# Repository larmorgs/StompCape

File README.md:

Stomp Cape
=======

Greg Larmore and Matt Moravec

This is the repository for the Stomp Cape--a BeagleBone cape for an open source guitar effects stomp pedal. The pedal will leverage the power of 32-bit embedded linux on the BeagleBone and will be reconfigurable using node.js.

Current Status
=======

Currently the schematic for the cape has been created and is being validated. Software to support the cape is under development.

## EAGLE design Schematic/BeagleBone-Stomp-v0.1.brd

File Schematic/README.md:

Stomp Cape
=======

Greg Larmore and Matt Moravec

This is the schematic for the Stomp Cape created in Eagle 6.3.0. It uses the built in Eagle libraries along with the libraries located in the ./lbr folder.

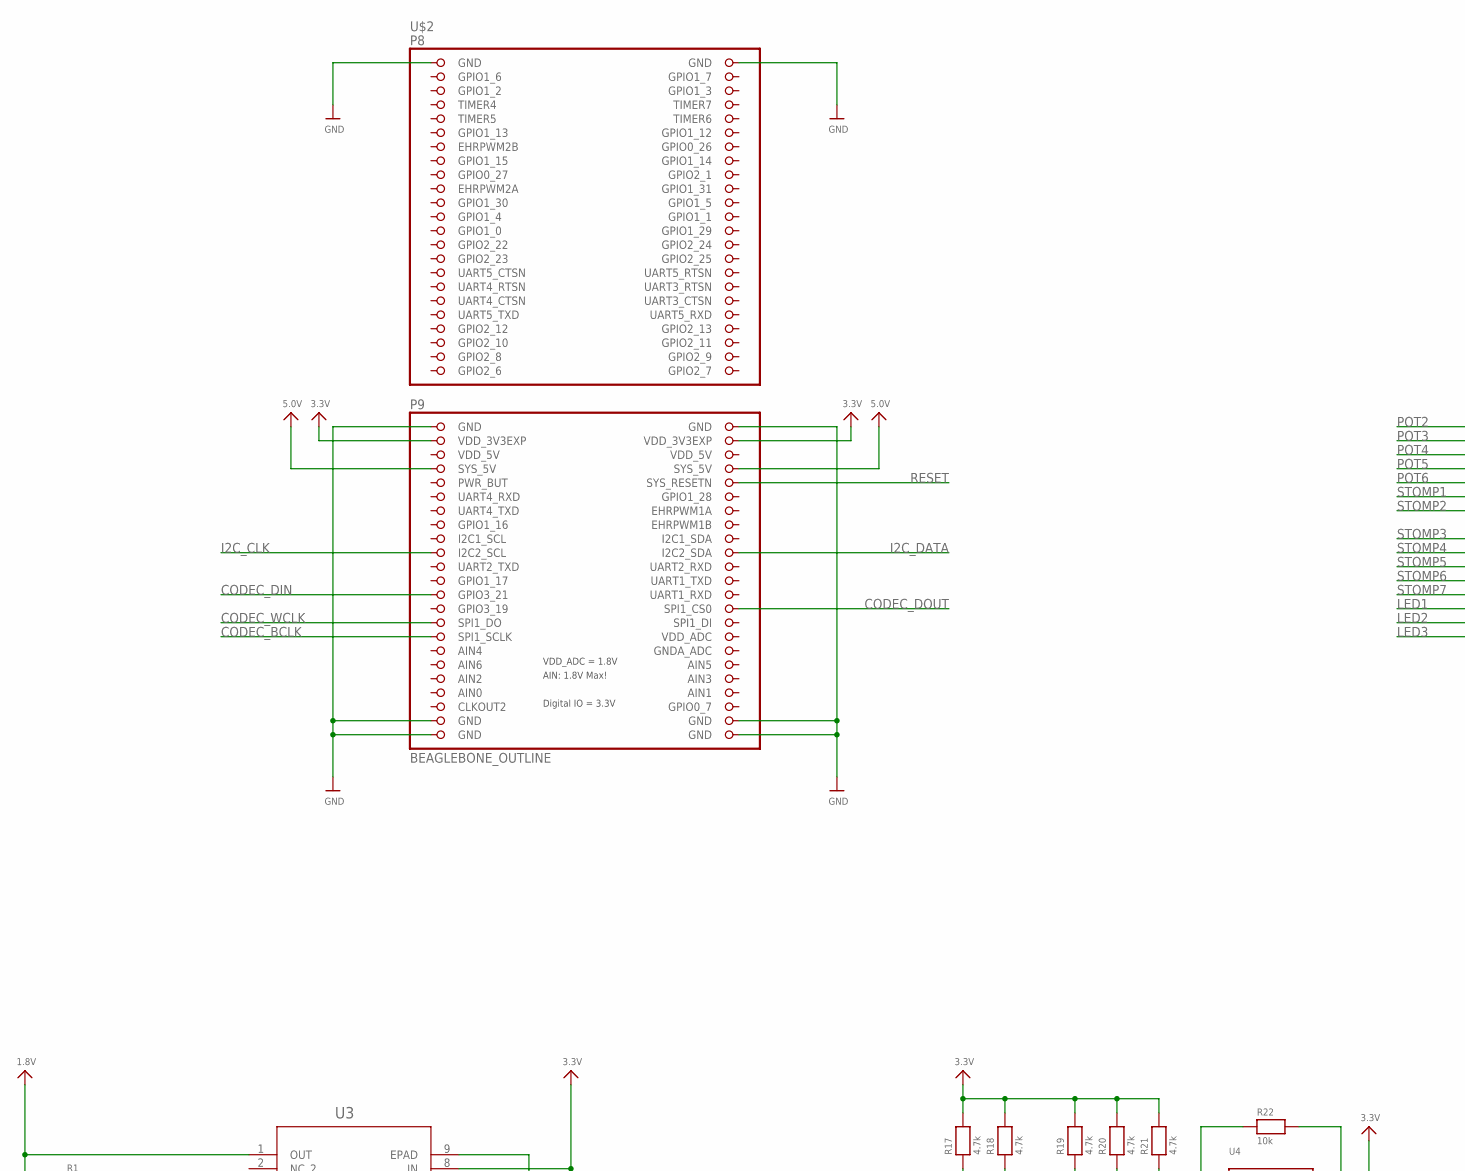
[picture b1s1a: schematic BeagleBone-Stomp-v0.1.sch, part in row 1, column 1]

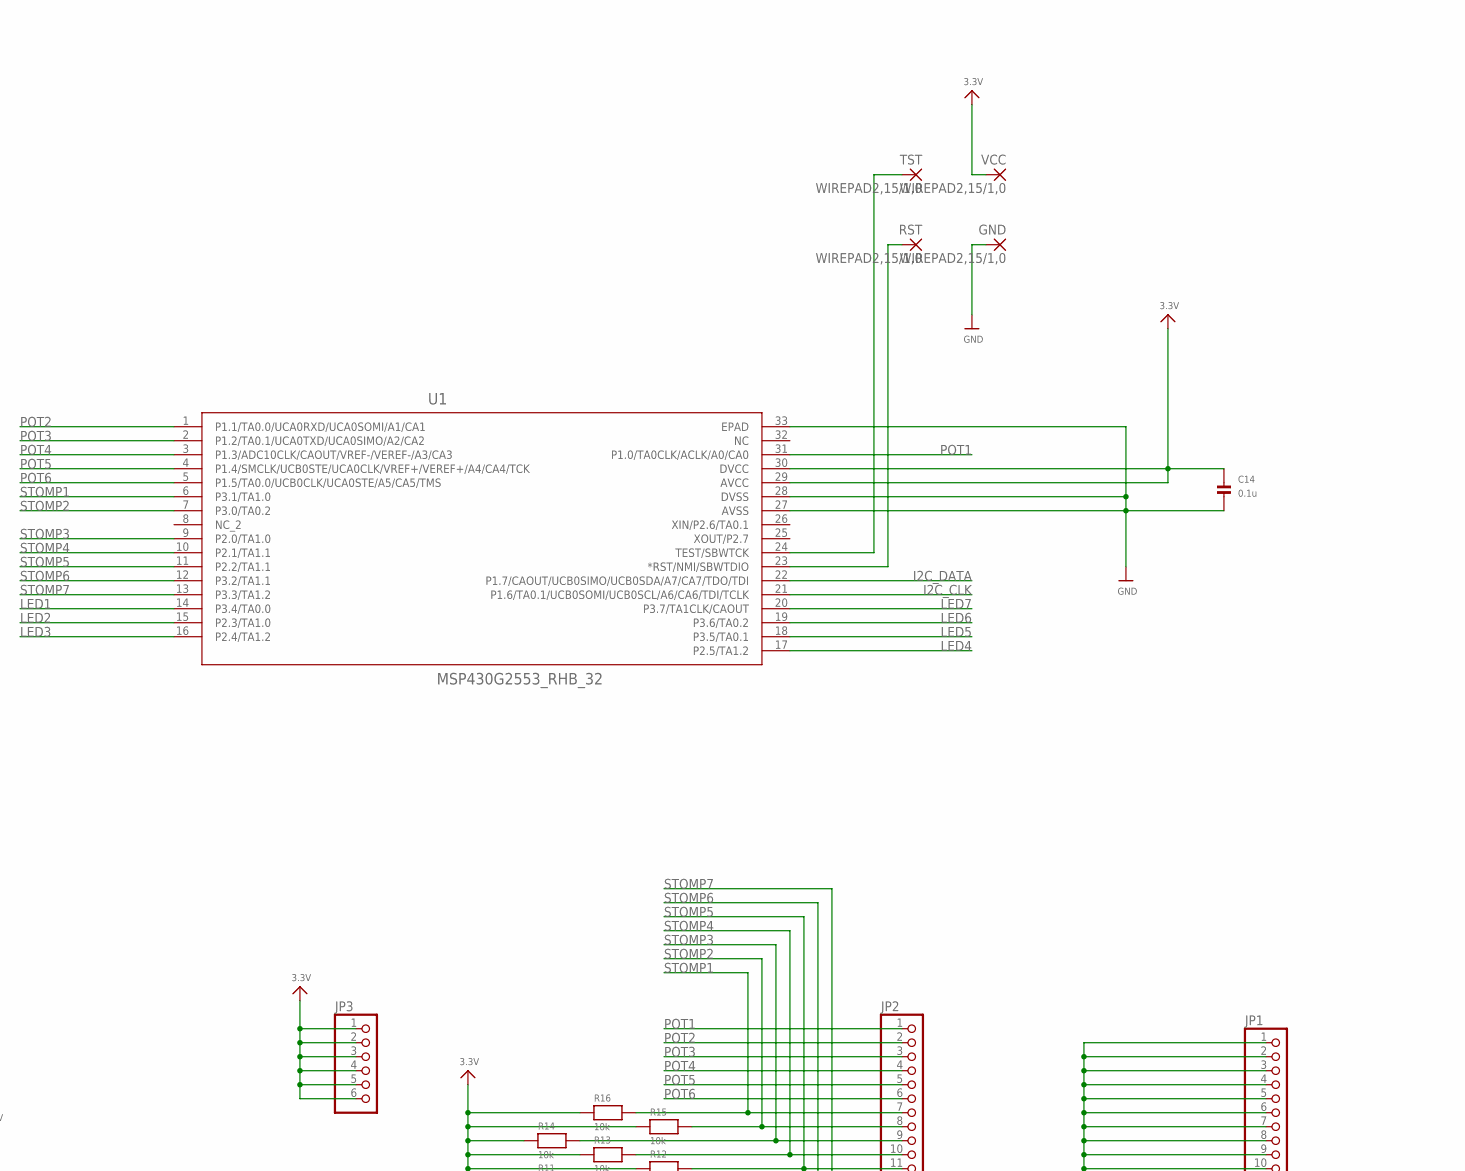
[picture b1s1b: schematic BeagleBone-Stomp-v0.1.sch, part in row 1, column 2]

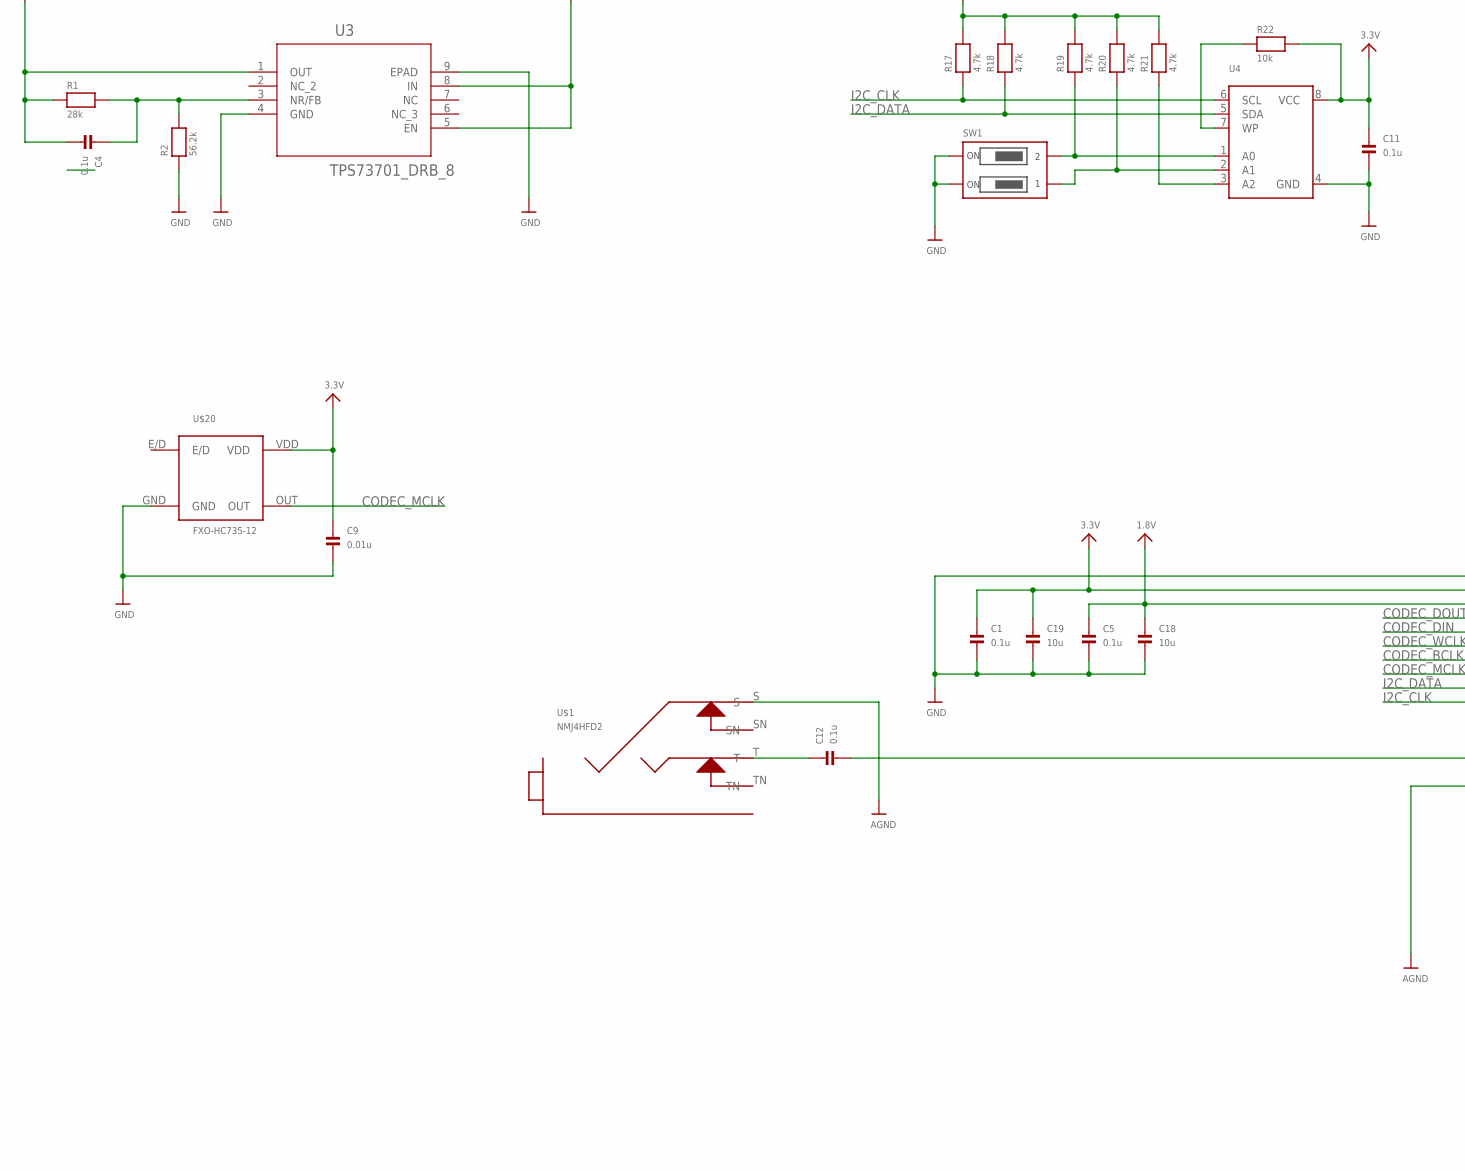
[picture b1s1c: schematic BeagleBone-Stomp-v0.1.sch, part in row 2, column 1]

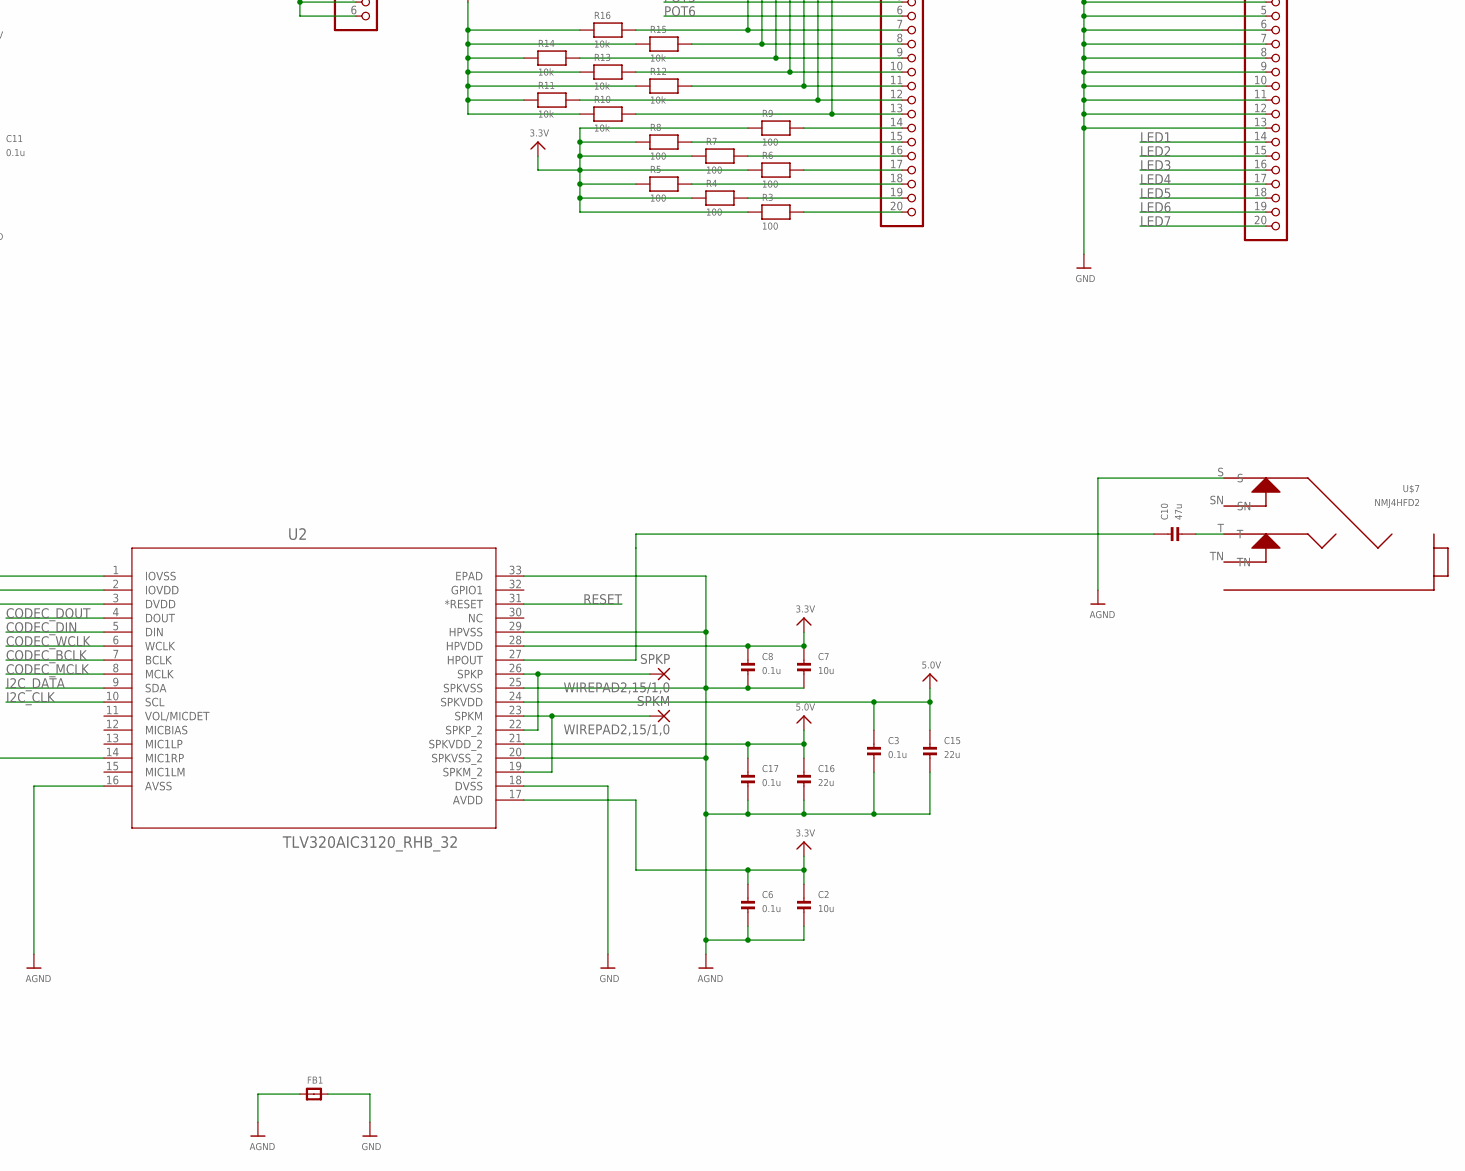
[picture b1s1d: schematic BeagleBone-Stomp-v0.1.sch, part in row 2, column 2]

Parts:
C1, C3, C4, C5, C6, C8, C11, C12, C14, C17: 0.1u; 0402
C2, C7, C18, C19: 10u; 0805
C9: 0.01u; 0402
C10: 47u; 0805
C15, C16: 22u; 0805
FB1: FERRITE_0402; _0402
GND: WIREPAD2,15/1,0; 2,15/1,0
JP1, JP2: HEADER-1X20ROUND; 1X20_ROUND
JP3: HEADER-1X6ROUND; 1X06_ROUND
R1: 28k; 0402
R2: 56.2k; 0402
R3, R4, R5, R6, R7, R8, R9: 100; 0402
R10, R11, R12, R13, R14, R15, R16, R22: 10k; 0402
R17, R18, R19, R20, R21: 4.7k; 0402
RST: WIREPAD2,15/1,0; 2,15/1,0
SPKM: WIREPAD2,15/1,0; 2,15/1,0
SPKP: WIREPAD2,15/1,0; 2,15/1,0
SW1: DIPSWITCH_2PIN
TST: WIREPAD2,15/1,0; 2,15/1,0
U1: MSP430G2553_RHB_32; RHB32_3P45X3P45
U2: TLV320AIC3120_RHB_32; RHB32_3P45X3P45
U3: TPS73701_DRB_8; DRB8_1P75X1P5
U4: EEPROM_I2C_SOIC8_GENERIC; SOIC8_150MIL
U$1, U$7: NMJ4HFD2
U$2: BEAGLEBONE_OUTLINE; BEAGLEBONE_SHIELD
U$20: FXO-HC735-12
VCC: WIREPAD2,15/1,0; 2,15/1,0

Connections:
1.8V: C4.2, C5.1, C18.1, R1.1, U2.3 (DVDD), U3.1 (OUT)
3.3V: C1.1, C2.1, C6.1, C7.1, C8.1, C9.1, C11.1, C14.1, C19.1, JP3.1, JP3.2, JP3.3, JP3.4, JP3.5, JP3.6, R3.1, R4.1, R5.1, R6.1, R7.1, R8.1, R9.1, R10.1, R11.1, R12.1, R13.1, R14.1, R15.1, R16.1, R17.2, R18.2, R19.2, R20.2, R21.2, R22.2, U1.29 (AVCC), U1.30 (DVCC), U2.2 (IOVDD), U2.17 (AVDD), U2.28 (HPVDD), U3.5 (EN), U3.8 (IN), U4.8 (VCC), U$2.49 (VDD_3V3EXP), U$2.50 (VDD_3V3EXP), U$20.VDD, VCC.1
5.0V: C3.1, C15.1, C16.1, C17.1, U2.21 (SPKVDD_2), U2.24 (SPKVDD), U$2.53 (SYS_5V), U$2.54 (SYS_5V)
AGND: C2.2, C3.2, C6.2, C7.2, C8.2, C15.2, C16.2, C17.2, FB1.1, U2.16 (AVSS), U2.20 (SPKVSS_2), U2.25 (SPKVSS), U2.29 (HPVSS), U2.33 (EPAD), U$1.S, U$7.S
CODEC_BCLK: U2.7 (BCLK), U$2.77 (SPI1_SCLK)
CODEC_DIN: U2.5 (DIN), U$2.71 (GPIO3_21)
CODEC_DOUT: U2.4 (DOUT), U$2.74 (SPI1_CS0)
CODEC_MCLK: U2.8 (MCLK), U$20.OUT
CODEC_WCLK: U2.6 (WCLK), U$2.75 (SPI1_DO)
GND: C1.2, C5.2, C9.2, C11.2, C14.2, C18.2, C19.2, FB1.2, GND.1, JP1.1, JP1.2, JP1.3, JP1.4, JP1.5, JP1.6, JP1.7, JP1.8, JP1.9, JP1.10, JP1.11, JP1.12, JP1.13, R2.1, SW1.1A, SW1.2A, U1.27 (AVSS), U1.28 (DVSS), U1.33 (EPAD), U2.1 (IOVSS), U2.18 (DVSS), U3.4 (GND), U3.9 (EPAD), U4.4 (GND), U$2.1 (GND), U$2.2 (GND), U$2.47 (GND), U$2.48 (GND), U$2.89 (GND), U$2.90 (GND), U$2.91 (GND), U$2.92 (GND), U$20.GND
GNDA_ADC: U$2.80 (GNDA_ADC)
I2C_CLK: R17.1, U1.21 (P1.6/TA0.1/UCB0SOMI/UCB0SCL/A6/CA6/TDI/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), U2.10 (SCL), U4.6 (SCL), U$2.65 (I2C2_SCL)
I2C_DATA: R18.1, U1.22 (P1.7/CAOUT/UCB0SIMO/UCB0SDA/A7/CA7/TDO/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), U2.9 (SDA), U4.5 (SDA), U$2.66 (I2C2_SDA)
LED1: JP1.14, U1.14 (P3.4/TA0.0)
LED2: JP1.15, U1.15 (P2.3/TA1.0)
LED3: JP1.16, U1.16 (P2.4/TA1.2)
LED4: JP1.17, U1.17 (P2.5/TA1.2)
LED5: JP1.18, U1.18 (P3.5/TA0.1)
LED6: JP1.19, U1.19 (P3.6/TA0.2)
LED7: JP1.20, U1.20 (P3.7/TA1CLK/CAOUT)
unnamed: C4.1, R1.2, R2.2, U3.3 (NR/FB)
unnamed: SPKM.1, U2.19 (SPKM_2), U2.23 (SPKM)
unnamed: SPKP.1, U2.22 (SPKP_2), U2.26 (SPKP)
unnamed: R19.1, SW1.1B, U4.1 (A0)
unnamed: C10.2, U$7.T
unnamed: JP2.20, R3.2
unnamed: C10.1, U2.27 (HPOUT)
unnamed: C12.1, U$1.T
unnamed: C12.2, U2.14 (MIC1RP)
unnamed: R20.1, SW1.2B, U4.2 (A1)
unnamed: R21.1, U4.3 (A2)
unnamed: JP2.14, R9.2
unnamed: JP2.15, R8.2
unnamed: JP2.16, R7.2
unnamed: JP2.17, R6.2
unnamed: R22.1, U4.7 (WP)
unnamed: JP2.18, R5.2
unnamed: JP2.19, R4.2
unnamed: TST.1, U1.24 (TEST/SBWTCK)
unnamed: RST.1, U1.23 (*RST/NMI/SBWTDIO)
POT1: JP2.1, U1.31 (P1.0/TA0CLK/ACLK/A0/CA0)
POT2: JP2.2, U1.1 (P1.1/TA0.0/UCA0RXD/UCA0SOMI/A1/CA1)
POT3: JP2.3, U1.2 (P1.2/TA0.1/UCA0TXD/UCA0SIMO/A2/CA2)
POT4: JP2.4, U1.3 (P1.3/ADC10CLK/CAOUT/VREF-/VEREF-/A3/CA3)
POT5: JP2.5, U1.4 (P1.4/SMCLK/UCB0STE/UCA0CLK/VREF+/VEREF+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)
POT6: JP2.6, U1.5 (P1.5/TA0.0/UCB0CLK/UCA0STE/A5/CA5/TMS)
RESET: U2.31 (*RESET), U$2.56 (SYS_RESETN)
STOMP1: JP2.7, R16.2, U1.6 (P3.1/TA1.0)
STOMP2: JP2.8, R15.2, U1.7 (P3.0/TA0.2)
STOMP3: JP2.9, R14.2, U1.9 (P2.0/TA1.0)
STOMP4: JP2.10, R13.2, U1.10 (P2.1/TA1.1)
STOMP5: JP2.11, R12.2, U1.11 (P2.2/TA1.1)
STOMP6: JP2.12, R11.2, U1.12 (P3.2/TA1.1)
STOMP7: JP2.13, R10.2, U1.13 (P3.3/TA1.2)
VDD_5V: U$2.51 (VDD_5V), U$2.52 (VDD_5V)
VDD_ADC: U$2.78 (VDD_ADC)

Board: 2 copper layers, 59 parts (0 on the bottom side), 54 nets, no tracks yet.

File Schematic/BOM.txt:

Partlist

Exported from BeagleBone-Stomp-v0.1.sch at 12/30/2012 6:02:00 PM

EAGLE Version 6.3.0 Copyright (c) 1988-2012 CadSoft

Assembly variant: 

Part     Value                Device                   Package           Library      Sheet

C1       0.1u                 CAP_CERAMIC0402          0402              microbuilder 1
C2       10u                  CAP_CERAMIC0805          0805              microbuilder 1
C3       0.1u                 CAP_CERAMIC0402          0402              microbuilder 1
C4       0.1u                 CAP_CERAMIC0402          0402              microbuilder 1
C5       0.1u                 CAP_CERAMIC0402          0402              microbuilder 1
C6       0.1u                 CAP_CERAMIC0402          0402              microbuilder 1
C7       10u                  CAP_CERAMIC0805          0805              microbuilder 1
C8       0.1u                 CAP_CERAMIC0402          0402              microbuilder 1
C9       0.01u                CAP_CERAMIC0402          0402              microbuilder 1
C10      47u                  CAP_CERAMIC0805          0805              microbuilder 1
C11      0.1u                 CAP_CERAMIC0402          0402              microbuilder 1
C12      0.1u                 CAP_CERAMIC0402          0402              microbuilder 1
C13      2.2u                 CAP_CERAMIC0402          0402              microbuilder 1
C14      0.1u                 CAP_CERAMIC0402          0402              microbuilder 1
C15      22u                  CAP_CERAMIC0805          0805              microbuilder 1
C16      22u                  CAP_CERAMIC0805          0805              microbuilder 1
C17      0.1u                 CAP_CERAMIC0402          0402              microbuilder 1
C18      10u                  CAP_CERAMIC0805          0805              microbuilder 1
C19      10u                  CAP_CERAMIC0805          0805              microbuilder 1
FB1                           FERRITE_0402             _0402             microbuilder 1
J1                            TC2030-MCP               TC2030-MCP        bone         1
J2       NMJ4HFD2             NMJ4HFD2                 NMJ4HFD2          bone         1
J3       NMJ4HFD2             NMJ4HFD2                 NMJ4HFD2          bone         1
JP1                           HEADER-1X20ROUND         1X20_ROUND        microbuilder 1
JP2                           HEADER-1X20ROUND         1X20_ROUND        microbuilder 1
JP3                           HEADER-1X6ROUND          1X06_ROUND        microbuilder 1
R1       28k                  RESISTOR0402             0402              microbuilder 1
R2       56.2k                RESISTOR0402             0402              microbuilder 1
R3       100                  RESISTOR0402             0402              microbuilder 1
R4       100                  RESISTOR0402             0402              microbuilder 1
R5       100                  RESISTOR0402             0402              microbuilder 1
R6       100                  RESISTOR0402             0402              microbuilder 1
R7       100                  RESISTOR0402             0402              microbuilder 1
R8       100                  RESISTOR0402             0402              microbuilder 1
R9       100                  RESISTOR0402             0402              microbuilder 1
R10      10k                  RESISTOR0402             0402              microbuilder 1
R11      10k                  RESISTOR0402             0402              microbuilder 1
R12      10k                  RESISTOR0402             0402              microbuilder 1
R13      10k                  RESISTOR0402             0402              microbuilder 1
R14      10k                  RESISTOR0402             0402              microbuilder 1
R15      10k                  RESISTOR0402             0402              microbuilder 1
R16      10k                  RESISTOR0402             0402              microbuilder 1
R17      4.7k                 RESISTOR0402             0402              microbuilder 1
R18      4.7k                 RESISTOR0402             0402              microbuilder 1
R19      4.7k                 RESISTOR0402             0402              microbuilder 1
R20      4.7k                 RESISTOR0402             0402              microbuilder 1
R21      4.7k                 RESISTOR0402             0402              microbuilder 1
R22      10k                  RESISTOR0402             0402              microbuilder 1
R23      47k                  RESISTOR0402             0402              microbuilder 1
S1       CTS-219-2MST         CTS-219-2MST             CTS-219-2MST      bone         1
SPKM     WIREPAD2,15/1,0      WIREPAD2,15/1,0          2,15/1,0          wirepad      1
SPKP     WIREPAD2,15/1,0      WIREPAD2,15/1,0          2,15/1,0          wirepad      1
U$5      BEAGLEBONE_OUTLINE   BEAGLEBONE_OUTLINE       BEAGLEBONE_SHIELD bone         1
U1       MSP430G2553_RHB_32   MSP430G2553_RHB_32       RHB32_3P45X3P45   bone         1
U2       TLV320AIC3120_RHB_32 TLV320AIC3120_RHB_32     RHB32_3P45X3P45   bone         1
U3       TPS73701_DRB_8       TPS73701_DRB_8           DRB8_1P75X1P5     bone         1
U4                            EEPROM_I2C_SOIC8_GENERIC SOIC8_150MIL      microbuilder 1
U5       FXO-HC735-12         FXO-HC735-12             FXO-HC735-12      bone         1

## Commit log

2012-12-03 Attempting to add files to Git repo
2012-12-03 Adding README
2012-12-06 connected a few of the pins in the design.
2012-12-16 Making some changes
2012-12-19 Adding MSP430 connections
2012-12-19 Adding datasheets and other docs
2012-12-27 Adding crystal and a couple caps. Also added codec connections
2012-12-28 Adding in EEPROM chip
2012-12-29 Pretty close to being done just need to check connections on schematic and make BOM
2012-12-29 Removing arrows and such
2012-12-31 Cleaning libraries up
2012-12-31 Adding BOM and netlist
2012-12-31 Cleaning up temp files
2012-12-31 Adding libraries with READMEs
2012-12-31 Making small changes
2012-12-31 Adding in README and another excel sheet for external stuff
2012-12-31 Adding in external components and dev tools
2012-12-31 Adding referenced docs and datasheets and cleaning up READMEs
2012-12-31 Adding a software folder
2012-12-31 Adding PDF of schematic and deleting a random wire that got added
2012-12-31 Updating Netlist and Schematic just to be sure
2012-12-31 Adding annotations (and names!) to schematic
